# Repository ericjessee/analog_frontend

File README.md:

Simple A/D and D/A board for FPGA DSP experimentation.

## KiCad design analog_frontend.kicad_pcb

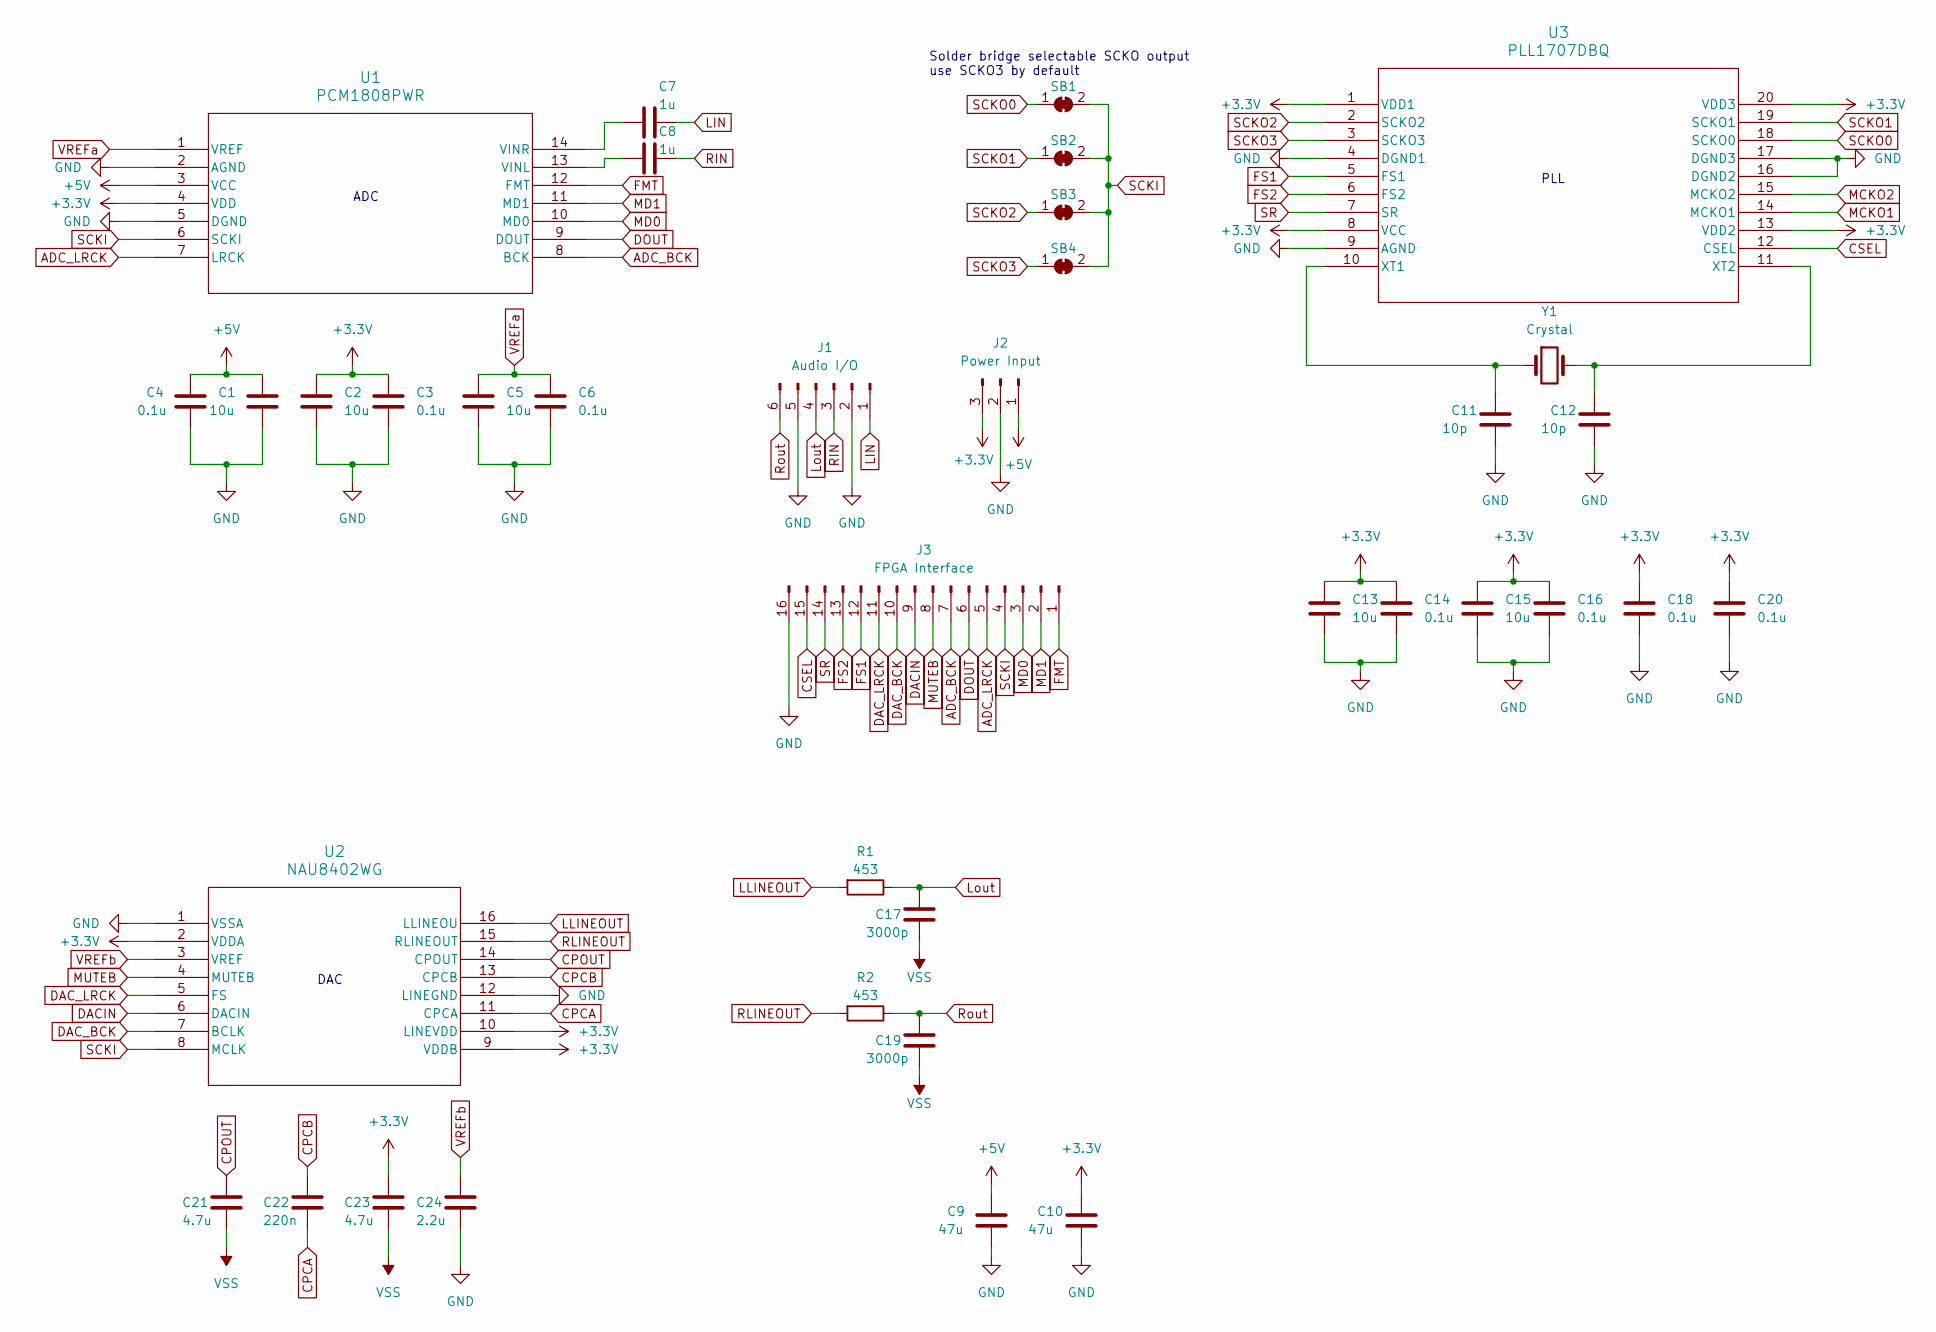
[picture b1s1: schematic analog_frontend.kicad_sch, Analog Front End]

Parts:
C1, C2, C5, C13, C15: 10u; C_0805_2012Metric
C3, C4, C6, C14, C16, C18, C20: 0.1u; C_0805_2012Metric
C7, C8: 1u; C_0805_2012Metric
C9, C10: 47u; CP_Radial_D6.3mm_P2.50mm
C11, C12: 10p; C_0805_2012Metric
C17, C19: 3000p; C_0805_2012Metric
C21, C23: 4.7u; C_0805_2012Metric
C22: 220n; C_0805_2012Metric
C24: 2.2u; C_0805_2012Metric
J1: Audio I/O; PinHeader_1x06_P2.54mm_Vertical
J2: Power Input; PinHeader_1x03_P2.54mm_Vertical
J3: FPGA Interface; PinHeader_1x16_P2.54mm_Vertical
R1, R2: 453; R_0805_2012Metric
SB1, SB2, SB3, SB4: SolderJumper_2_Bridged; SolderJumper-2_P1.3mm_Open_TrianglePad1.0x1.5mm
U1: PCM1808PWR; TSSOP-14_4.4x5mm_P0.65mm
U2: NAU8402WG; TSSOP-16_4.4x5mm_P0.65mm
U3: PLL1707DBQ; QSOP-20_3.9x8.7mm_P0.635mm
Y1: Crystal; Crystal_SMD_3225-4Pin_3.2x2.5mm

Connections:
+3.3V: C2.1, C3.1, C10.1, C13.1, C14.1, C15.1, C16.1, C18.1, C20.1, C23.2, J2.3, U1.4 (VDD), U2.2 (VDDA), U2.9 (VDDB), U2.10 (LINEVDD), U3.1 (VDD1), U3.8 (VCC), U3.13 (VDD2), U3.20 (VDD3)
+5V: C1.1, C4.1, C9.1, J2.1, U1.3 (VCC)
ADC_BCK: J3.7, U1.8 (BCK)
ADC_LRCK: J3.5, U1.7 (LRCK)
CPCA: C22.1, U2.11 (CPCA)
CPCB: C22.2, U2.13 (CPCB)
CPOUT: C21.2, U2.14 (CPOUT)
CSEL: J3.15, U3.12 (CSEL)
DACIN: J3.9, U2.6 (DACIN)
DAC_BCK: J3.10, U2.7 (BCLK)
DAC_LRCK: J3.11, U2.5 (FS)
DOUT: J3.6, U1.9 (DOUT)
FMT: J3.1, U1.12 (FMT)
FS1: J3.12, U3.5 (FS1)
FS2: J3.13, U3.6 (FS2)
GND: C1.2, C2.2, C3.2, C4.2, C5.2, C6.2, C9.2, C10.2, C11.2, C12.2, C13.2, C14.2, C15.2, C16.2, C18.2, C20.2, C24.1, J1.2, J1.5, J2.2, J3.16, U1.2 (AGND), U1.5 (DGND), U2.1 (VSSA), U2.12 (LINEGND), U3.4 (DGND1), U3.9 (AGND), U3.16 (DGND2), U3.17 (DGND3)
LIN: C7.2, J1.1
LLINEOUT: R1.2, U2.16 (LLINEOU)
Lout: C17.2, J1.4, R1.1
MCKO1: U3.14 (MCKO1)
MCKO2: U3.15 (MCKO2)
MD0: J3.3, U1.10 (MD0)
MD1: J3.2, U1.11 (MD1)
MUTEB: J3.8, U2.4 (MUTEB)
unnamed: C8.1, U1.13 (VINL)
unnamed: C7.1, U1.14 (VINR)
unnamed: C11.1, U3.10 (XT1), Y1.1
unnamed: C12.1, U3.11 (XT2), Y1.3
RIN: C8.2, J1.3
RLINEOUT: R2.2, U2.15 (RLINEOUT)
Rout: C19.2, J1.6, R2.1
SCKI: J3.4, SB1.2 (B), SB2.2 (B), SB3.2 (B), SB4.2 (B), U1.6 (SCKI), U2.8 (MCLK)
SCKO0: SB1.1 (A), U3.18 (SCKO0)
SCKO1: SB2.1 (A), U3.19 (SCKO1)
SCKO2: SB3.1 (A), U3.2 (SCKO2)
SCKO3: SB4.1 (A), U3.3 (SCKO3)
SR: J3.14, U3.7 (SR)
VREFa: C5.1, C6.1, U1.1 (VREF)
VREFb: C24.2, U2.3 (VREF)
VSS: C17.1, C19.1, C21.1, C23.1

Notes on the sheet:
PLL
DAC
Solder bridge selectable SCKO output use SCKO3 by default
ADC

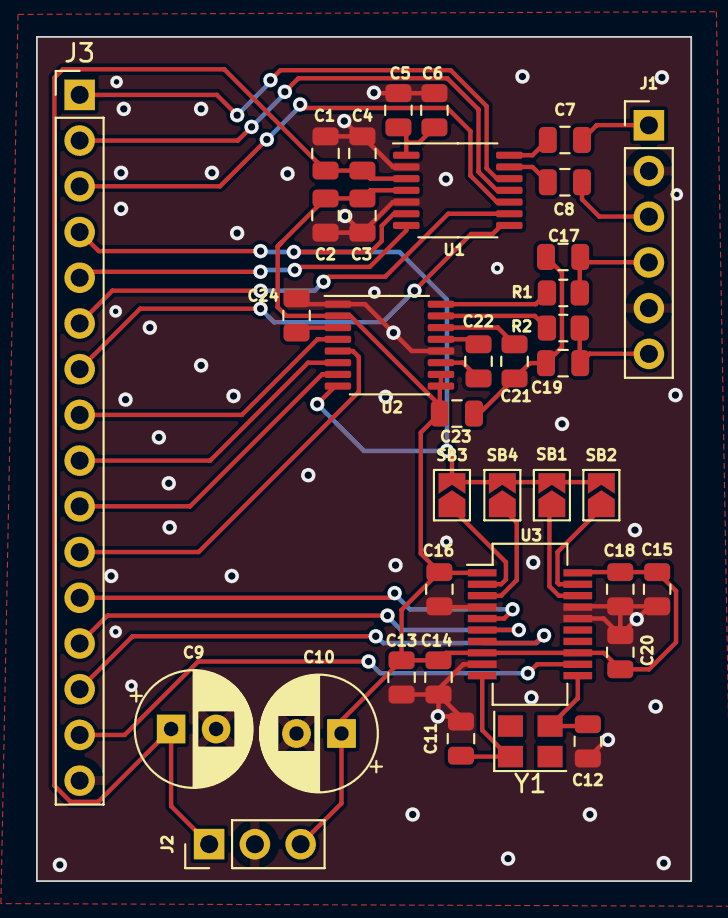
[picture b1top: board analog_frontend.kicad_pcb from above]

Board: 2 copper layers, 36.4 x 46.9 mm, 37 parts (0 on the bottom side), 38 nets.
